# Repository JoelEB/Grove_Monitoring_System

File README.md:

# Grove_Monitoring_System
Controlling the Grove motherboard over I2C

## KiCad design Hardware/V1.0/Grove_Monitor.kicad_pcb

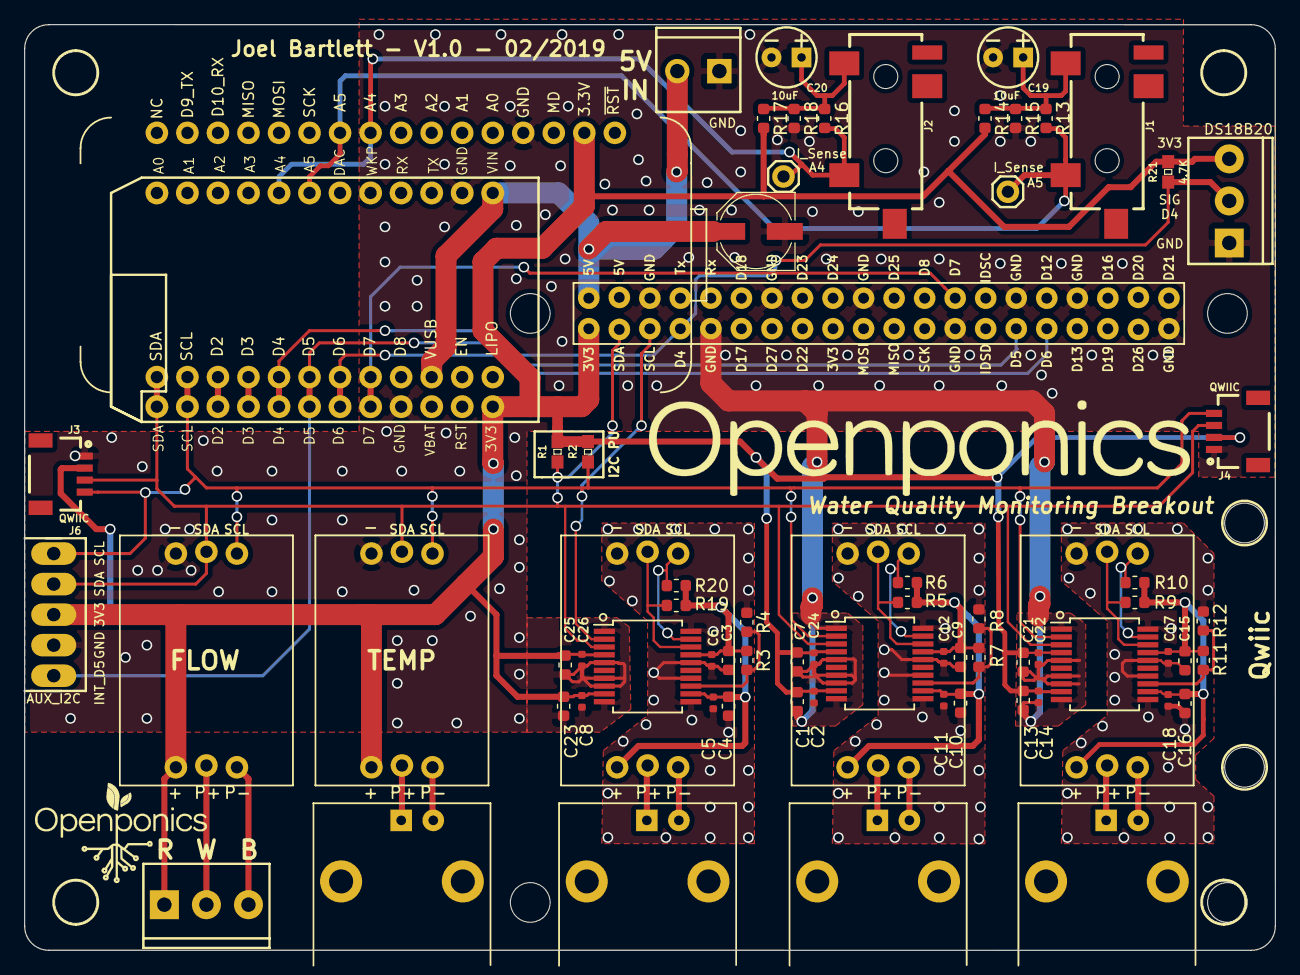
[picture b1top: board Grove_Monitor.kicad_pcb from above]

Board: 2 copper layers, 104.0 x 77.0 mm, 83 parts (1 on the bottom side), 40 nets.

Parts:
C1, C3, C4, C7, C9, C10, C13, C15, C16, C21, C23, C25: 10uF; C_0603_1608Metric
C2, C5, C6, C8, C11, C12, C14, C17, C18, C22, C24, C26: 0.1uF; C_0402_1005Metric
C19, C20: 10uF; CPOL-RADIAL-2.5MM-5MM
C101: 470µF; PANASONIC_D
H1, H2, H3, H4: STAND-OFF; STAND-OFF_LARGE
H5, H6: STAND-OFF
J1, J2: AUDIO_JACK_3.5MM_SMD; AUDIO-JACK-3.5MM-SMD
J3, J4: QWIIC; Qwiic_Connector
J5, J7: Conn_01x03; SCREWTERMINAL-3.5MM-3
J6: Conn_01x05; 1X05_LONGPADS
J8: Conn_01x02; SCREWTERMINAL-3.5MM-2
J9, J10: Conn_01x01; 1X01
JP1: PARTICLE_PHOTON
LOGO1: OPENPONICS_LOGO; Openponics_Logo_Plain_45mm
LOGO2: OPENPONICS_LOGO; Openponics_Logo_Horizontal_16mm
LOGO3: OPENPONICS_LOGO; Openponics_Logo_Horizontal_3_inch
P1, P2, P3, P401: BNC; WL-EB08040502_snk
PI_BOARD101: RASPBERRY_PI_2; RasPi-40pin_Connector
PI_Board: VAL**; RAS_PI_MOUNTING_HOLES
R1, R2, R21: 4.7K; 0603
R3, R7, R11: 16.9K; R_0603_1608Metric
R4, R8, R12: 10K; R_0603_1608Metric
R5, R6, R9, R10, R19, R20: 4.7K; R_0603_1608Metric
R13, R16: 100; R_0603_1608Metric
R14, R15, R17, R18: 10k; R_0603_1608Metric
STP1, STP2, STP3, STP4, STP401: ATLAS_STAMP; ATLAS_STAMP_EZO
U1: PARTICLE_MESH; Particle_Mesh
U2, U3, U4: ADM3260; SSOP-20_5.3x7.2mm_P0.65mm

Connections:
+3V3: C1.1, C2.1, C7.1, C8.1, C13.1, C14.1, C21.1, C22.1, C23.1, C24.1, C25.1, C26.1, J3.2, J4.2, J5.1, J6.3, J7.3, JP1.24, PI_BOARD101.1, R1.2, R2.2, R14.2, R17.2, R21.2, STP4.4, STP401.4, U1.2, U2.4, U2.9, U3.4, U3.9, U4.4, U4.9
+5V: C101.1, J8.2, JP1.1, PI_BOARD101.2, U1.26
/ADM3260_ISO_1/SCL_ISO: R20.2, STP1.3, U2.19
/ADM3260_ISO_1/SDA_ISO: R19.2, STP1.2, U2.18
/ADM3260_ISO_1/VSEL: R3.2, R4.1, U2.13
/ADM3260_ISO_2/SCL_ISO: R6.2, STP2.3, U3.19
/ADM3260_ISO_2/SDA_ISO: R5.2, STP2.2, U3.18
/ADM3260_ISO_2/VSEL: R7.2, R8.1, U3.13
/ADM3260_ISO_3/SCL_ISO: R10.2, STP3.3, U4.19
/ADM3260_ISO_3/SDA_ISO: R9.2, STP3.2, U4.18
/ADM3260_ISO_3/VSEL: R11.2, R12.1, U4.13
/PROBE: J5.2, STP4.5
/P_GND: J5.3, STP4.6
A4: J2.TIP, J10.1, JP1.8, R16.2, U1.9
A5: J1.TIP, J9.1, JP1.7, R13.2, U1.10
D2: JP1.15, U1.19
D3: JP1.16, U1.20
D4: J7.2, JP1.17, PI_BOARD101.7, R21.1, U1.21
D5: J6.1, JP1.18, PI_BOARD101.29, U1.22
D6: JP1.19, PI_BOARD101.31, U1.23
D7: JP1.20, PI_BOARD101.26, U1.24
GND: C1.2, C2.2, C7.2, C8.2, C13.2, C14.2, C19.2, C20.2, C21.2, C22.2, C23.2, C24.2, C25.2, C26.2, C101.2, J3.1, J4.1, J6.2, J7.1, J8.1, JP1.2, JP1.21, PI_BOARD101.6, PI_BOARD101.9, PI_BOARD101.14, PI_BOARD101.20, PI_BOARD101.25, PI_BOARD101.30, PI_BOARD101.34, PI_BOARD101.39, R15.2, R18.2, STP4.1, STP401.1, U1.4, U2.1, U2.5, U2.7, U2.8, U2.10, U3.1, U3.5, U3.7, U3.8, U3.10, U4.1, U4.5, U4.7, U4.8, U4.10
GND_ISO1: C3.2, C4.2, C5.2, C6.2, R4.2, STP1.1, U2.11, U2.14, U2.16, U2.20
GND_ISO2: C9.2, C10.2, C11.2, C12.2, R8.2, STP2.1, U3.11, U3.14, U3.16, U3.20
GND_ISO3: C15.2, C16.2, C17.2, C18.2, R12.2, STP3.1, U4.11, U4.14, U4.16, U4.20
unnamed: C19.1, J1.SLEE, R13.1, R14.1, R15.1
unnamed: C20.1, J2.SLEE, R16.1, R17.1, R18.1
unnamed: P1.1, STP1.5
unnamed: P1.2, STP1.6
unnamed: P2.1, STP2.5
unnamed: P2.2, STP2.6
unnamed: P3.1, STP3.5
unnamed: P3.2, STP3.6
unnamed: P401.1, STP401.5
unnamed: P401.2, STP401.6
SCL: J3.4, J4.4, J6.5, JP1.14, PI_BOARD101.5, R2.1, STP4.3, STP401.3, U1.18, U2.2, U3.2, U4.2
SDA: J3.3, J4.3, J6.4, JP1.13, PI_BOARD101.3, R1.1, STP4.2, STP401.2, U1.17, U2.3, U3.3, U4.3
VCC_ISO1: C3.1, C4.1, C5.1, C6.1, R3.1, R19.1, R20.1, STP1.4, U2.12, U2.17
VCC_ISO2: C9.1, C10.1, C11.1, C12.1, R5.1, R6.1, R7.1, STP2.4, U3.12, U3.17
VCC_ISO3: C15.1, C16.1, C17.1, C18.1, R9.1, R10.1, R11.1, STP3.4, U4.12, U4.17

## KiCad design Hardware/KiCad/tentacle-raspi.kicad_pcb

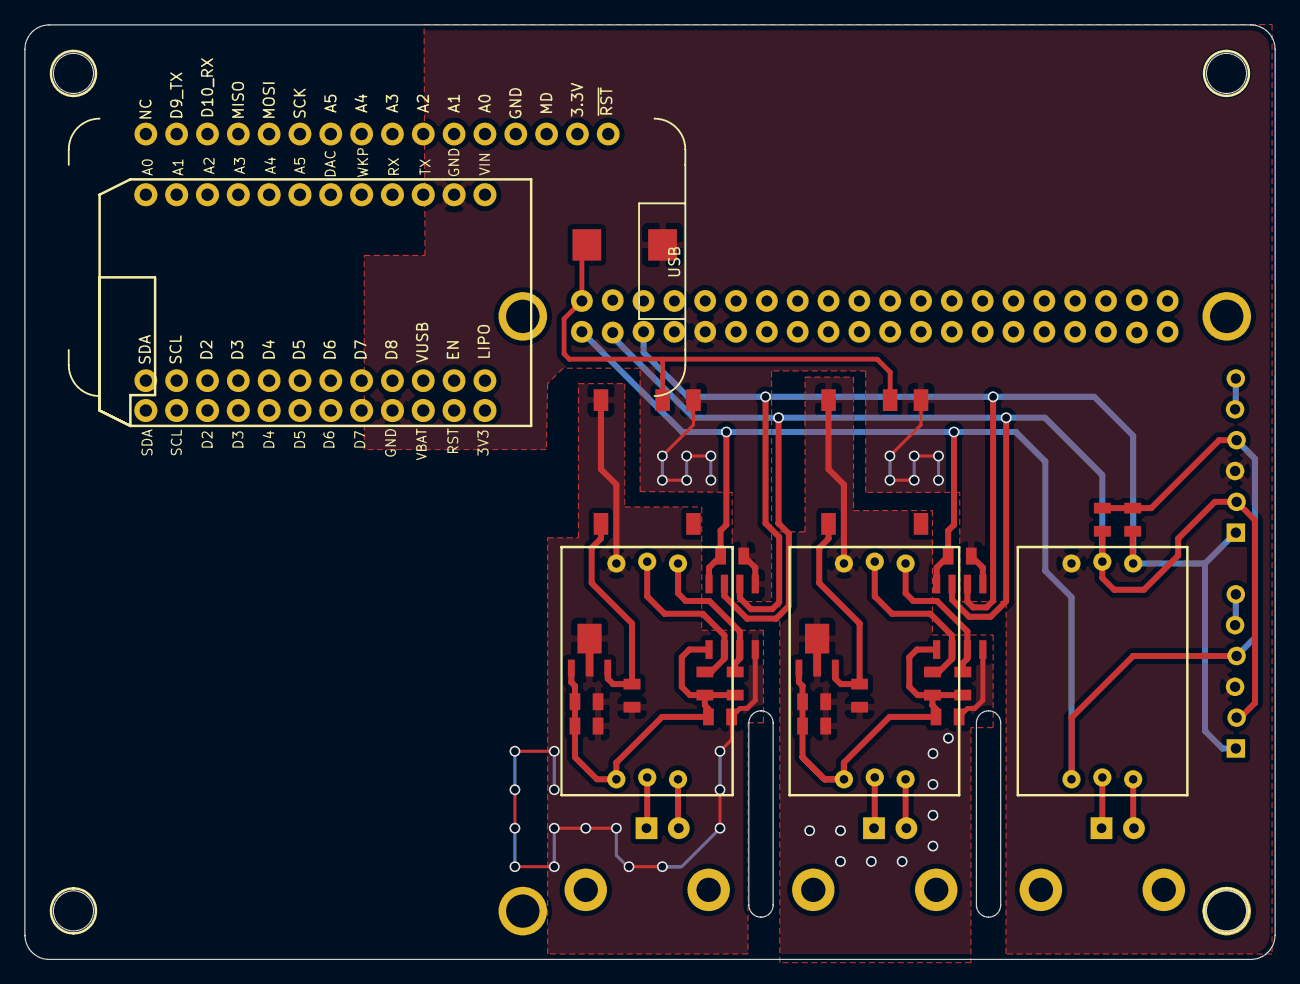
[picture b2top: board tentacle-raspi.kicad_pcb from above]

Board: 2 copper layers, 103.0 x 77.0 mm, 39 parts (0 on the bottom side), 23 nets.

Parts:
C101: 470µF; WL-CASE-X-2917
C201, C202, C301, C302: 1µF; WL-SM0805C
C203, C303: 2.2µF; WL-SM0805C
C204, C205, C304, C305: 0.1 µF; WL-SM0805C
DCDC201, DCDC301: R1SE_0505; WL-R1SE-0505
H1, H2, H3, H4: STAND-OFF
JP1: PARTICLE_PHOTON
P101, P102: CONN_01X06; WL-PINH_1X6_snk
P201, P301, P401: BNC; WL-EB08040502_snk
PI_BOARD101: RASPBERRY_PI_2; WL-40pin_snk
PI_Board: VAL**; WL-PI_Board_no_outline
R101, R102, R201, R202, R301, R302: 4.7K; WL-SM0805R
REG201, REG301: LD2981ABU50TR; WL-SOT89
SIG_ISO201, SIG_ISO301: SI8600; WL-SOIC8N
STP201, STP301, STP401: ATLAS_STAMP; WL-ezo-19454_snk
U1: PARTICLE_MESH; Particle_Mesh

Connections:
+3V3: C205.1, C305.1, JP1.24, P101.4, P102.4, PI_BOARD101.1, R101.2, R102.2, SIG_ISO201.8, SIG_ISO301.8, STP401.4
/SCL: P101.1, P102.1, PI_BOARD101.5, R102.1, SIG_ISO201.6, SIG_ISO301.6, STP401.3
/SDA: P101.2, P102.2, PI_BOARD101.3, R101.1, SIG_ISO201.7, SIG_ISO301.7, STP401.2
GND: C101.2, C205.2, C305.2, DCDC201.1, DCDC301.1, JP1.2, JP1.21, P101.3, P102.3, PI_BOARD101.9, SIG_ISO201.5, SIG_ISO301.5, STP401.1
GND_ISO2: C201.1, C202.1, C203.1, C204.1, DCDC201.4, REG201.2, SIG_ISO201.4, STP201.1
GND_ISO3: C301.1, C302.1, C303.1, C304.1, DCDC301.4, REG301.2, SIG_ISO301.4, STP301.1
unnamed: C202.2, DCDC201.5, REG201.3
unnamed: C302.2, DCDC301.5, REG301.3
unnamed: P101.5, P101.6
unnamed: P102.5, P102.6
unnamed: P201.1, STP201.5
unnamed: P201.2, STP201.6
unnamed: P301.1, STP301.5
unnamed: P301.2, STP301.6
unnamed: P401.1, STP401.5
unnamed: P401.2, STP401.6
unnamed: R201.2, SIG_ISO201.3, STP201.3
unnamed: R202.2, SIG_ISO201.2, STP201.2
unnamed: R301.2, SIG_ISO301.3, STP301.3
unnamed: R302.2, SIG_ISO301.2, STP301.2
VCC: C101.1, DCDC201.2, DCDC301.2, JP1.1, PI_BOARD101.2
V_ISO2: C201.2, C203.2, C204.2, R201.1, R202.1, REG201.1, SIG_ISO201.1, STP201.4
V_ISO3: C301.2, C303.2, C304.2, R301.1, R302.1, REG301.1, SIG_ISO301.1, STP301.4

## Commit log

2018-12-09 Alterations begun on t3 Tentacle shield
2018-12-09 Adding Firmware
2018-12-09 Major changes to node-red dash interface and particle code
2018-12-09 V1 - Flow and Partilce code a good point
2019-02-22 V0.1 mostly finished, ready for review and then ordering.
2019-02-28 V1.0 Complete
2019-06-27 Updating flows
2019-11-22 Adding V1.1 Folder
